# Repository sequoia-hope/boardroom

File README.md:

# Boardroom

**Boardroom is the home of a board design suite**: KiCad boards designed with
[Claude Code](https://claude.com/claude-code), from requirements to fab outputs. It holds the
design skill, the board project template, and the app that lists your projects and launches the
other suite apps. It also defines the format every board repo in the suite follows.

> **Migration under way (2026-11).** Boardroom is becoming one program with many crates:
> Projects, Compose and Route as modes of one app, with the router rewritten here
> ([`docs/one-system-spec.md`](docs/one-system-spec.md)). So far: one Cargo workspace (`crates/`),
> the web app at `web/`, pcbview in the tree as `view/`, and no submodules. The KiCad reader, the
> board model, the renderer and the intent, recognition and judging crates are in (`crates/kicad`,
> `board`, `scene`, `render`, `wasm`, `intent`, `recognise`, `library`, `interfaces`, `examine`),
> with Composer's `packages/` and `library/`. Not
> working until their crates arrive: Compose and Route. Sections below that describe
> separate repos and submodules describe board repos made so far, which stay on their pins.

**Try it:** [sequoia-hope.github.io/boardroom](https://sequoia-hope.github.io/boardroom/) is a
read-only copy of the app, open on the worked example, easy2350.

**For an agent pointed here:** this README is the map. It says what each project in the suite is,
where its repo and live page are, what a board repo looks like, and how to make one that works
with the viewer, the router and the other apps. Follow the links for detail. The specs under
[`docs/`](docs/) are the full design; [`CLAUDE.md`](CLAUDE.md) holds the rules for this repo, and
[`template/CLAUDE.md`](template/CLAUDE.md) holds the rules for a board repo.

## The suite

| Project | What it does | Repo | Live page | How a board repo uses it |
|---|---|---|---|---|
| **Boardroom** | Design skill, project template and phase gates. The app is the suite's main window: project list, status, the other apps in tabs | [sequoia-hope/boardroom](https://github.com/sequoia-hope/boardroom) | [app demo](https://sequoia-hope.github.io/boardroom/) | **`scripts/new-board.sh` makes a board repo** from `template/`, the skill and the pinned submodules |
| **pcbview** | Schematic, PCB and 3D viewer for KiCad boards, laid out after Altium 365's. Output is a static site that runs on GitHub Pages | [sequoia-hope/pcbview](https://github.com/sequoia-hope/pcbview) | in use: [robot-link](https://sequoia-hope.github.io/robot-link/), [round-pendant](https://sequoia-hope.github.io/round-pendant/) | **Git submodule** at `vendor/pcbview`, built by `scripts/view.sh` |
| **UltraRoute** | KiCad autorouter (`ultraroute route`, Rust, MIT), judged by KiCad's own DRC. **UltraRoute Studio** is its live, interactive view | [sequoia-hope/ultraroute](https://github.com/sequoia-hope/ultraroute) | [Studio](https://sequoia-hope.github.io/ultraroute/) (routes in the browser, WASM) | **Git submodule** at `vendor/ultraroute`, built by `scripts/route.sh` on first use |
| **Circuit Composer** | The stage between schematic and routing: verified chip packages, cited intent files, floorplanning, locked critical blocks, rules and cost grids for the router | [sequoia-hope/circuit-composer](https://github.com/sequoia-hope/circuit-composer) | [app](https://sequoia-hope.github.io/circuit-composer/) | **A tool you install** (`ccomp` CLI and its app). It reads `design/nets.csv` and writes under `compose/` |
| **Waffle Iron** | Parametric mechanical CAD in the browser: enclosures and mechanics around the board | [sequoia-hope/waffle-iron](https://github.com/sequoia-hope/waffle-iron) | [app](https://sequoia-hope.github.io/waffle-iron/) | **A linked project**, usually its own repo. Shares the board outline through `interface/` |
| **board-interface** | Rust crate that reads, writes, hashes and compares the shared board outline files (`board-shape.dxf` + `.json`) | [sequoia-hope/board-interface](https://github.com/sequoia-hope/board-interface) | | **Used by the apps, not the board repo.** Composer and Waffle Iron pin a tag of it |
| **board-draw** | Rust/WASM and WebGL2 board renderer shared by Studio and Composer, so both draw a board the same way | [sequoia-hope/board-draw](https://github.com/sequoia-hope/board-draw) | | **Used by the apps, not the board repo** |

**Submodule or not:** a board repo pins only the tools its own files depend on, **pcbview and
ultraroute**, as git submodules. A route depends on the exact router version, so pinning it per
project is deliberate. Circuit Composer and Waffle Iron are apps that open the board repo. They
are not vendored into it. board-interface and board-draw are libraries inside those apps.

### How the pieces connect

The apps talk through the board repo's files, never through each other's internals.
**KiCad files are the shared truth** for the schematic and the board. Each app owns its own
directory and doesn't write in another's.

```
requirements ─▶ Boardroom skill: phases 0–3 ─▶ hw/<board>/<variant>/*.kicad_sch, design/nets.csv
                                                   │
                     Circuit Composer (ccomp) ◀────┘  intent, packages, floorplan, locked blocks
                                │                     ─▶ compose/<board>/, placed .kicad_pcb
                                ▼
                     UltraRoute (route.sh / Studio)   routes the rest ─▶ routed .kicad_pcb
                                │
                                ▼
          Boardroom skill: phases 8–10, pcbview build ─▶ viewer/, fab outputs, index.html

          Waffle Iron ◀──── interface/<board>/board-shape.{dxf,json} ────▶ Circuit Composer
                       (board outline: one side drives, the other is locked until it takes over)
```

## A board repo

Every board in the suite lives in a repo with this layout. `scripts/new-board.sh` assembles it
from `template/` plus the copied skill (`.claude/skills/pcb-design/`), shared scripts
(`scripts/{doctor,view,route}.sh`), and pinned submodules (`vendor/{pcbview,ultraroute}`):

```
CLAUDE.md                    tells Claude to use the skill and follow its gates
.claude/skills/pcb-design/   the design skill, vendored: phases, gate checklists, review prompts, LESSONS.md
design/
  status.json                headline state: phase, what Claude is doing, what it needs from you, gates, checks
  intent.md                  requirements, each numbered (phase 0)
  nets.csv                   net classes (phase 3; Circuit Composer imports it)
  decisions.md               why each choice was made
  gates/                     one file per passed gate, with real tool output as evidence
  links.toml                 links to Waffle Iron projects (suite spec; planned)
hw/<board>/<variant>/        KiCad projects, one per board variant, e.g. hw/main/a/
compose/<board>/             Circuit Composer's files (written by Composer only)
route/<board>/               UltraRoute Studio's jobs and route recipe
interface/<board>/           board-shape.dxf + board-shape.json, the shared outline (written only by board-interface)
pcbview.toml                 which boards the viewer builds, and which one index.html embeds
index.html                   the project page: status from design/status.json, plus the embedded viewer
vendor/pcbview/              submodule: the viewer
vendor/ultraroute/           submodule: the autorouter
scripts/doctor.sh            checks KiCad, Python and the rest are installed
scripts/view.sh              builds the viewer
scripts/route.sh             builds and runs the router
serve.sh                     serves the project page: ./serve.sh --port N
```

Rules an agent must keep:

- **Never edit `vendor/` or `viewer/` by hand.** Bump a submodule to change a tool, and rebuild
  the viewer to change `viewer/`.
- **Update `design/status.json` and rebuild the viewer at every gate.** The Boardroom app and
  `index.html` both read `status.json`. Its version 1 schema is in
  [`docs/shell-spec.md`](docs/shell-spec.md#statusjson-version-1). Each app writes only under its
  own `apps.<name>` key.
- **Ports come from the caller.** `serve.sh` takes `--port`, then `$PORT`, and fails if it has
  neither. Don't hardcode one.
- **Corrections become lessons.** When the person corrects Claude, the rule goes into
  `.claude/skills/pcb-design/LESSONS.md`.

Repos made this way: [easy2350](examples/easy2350/) (in this repo, the worked example),
[simple-earring](https://github.com/sequoia-hope/simple-earring).

## Start a board

1. **Make your repo.** Clone Boardroom with its submodules, then run `scripts/new-board.sh`:
   ```sh
   git clone --recurse-submodules https://github.com/sequoia-hope/boardroom
   cd boardroom
   scripts/new-board.sh ~/pcb/my-board --name "My board"
   cd ~/pcb/my-board
   ```
   Pass `--github <you>/<my-board>` (and `--private` if private) to create the GitHub repo and
   push in the same step:
   ```sh
   scripts/new-board.sh ~/pcb/my-board --name "My board" --github <you>/<my-board>
   ```
   If `~/.config/boardroom/projects.toml` exists, `new-board.sh` adds the new folder to it.

2. **Check your tools.**
   ```sh
   scripts/doctor.sh
   ```
   You need KiCad 9+ (`kicad-cli`), Python 3.11+ and numpy. KiCad's Python module and ngspice
   are recommended. Routing needs Rust (`cargo`).

3. **Serve the project page** in a second terminal:
   ```sh
   ./serve.sh --port N
   ```
   and open `http://localhost:N/`. To check from your phone, use the machine's address on your
   network instead of `localhost`.

4. **Start Claude Code** in the repo and describe the board:
   ```sh
   claude
   > Let's design a board: a USB-C powered controller for two 12 V DC motors, about 50 × 80 mm.
   ```
   Claude starts at phase 0 and asks about everything the description leaves open. It stops for
   your sign-off at phases 0, 4 and 10, and whenever `design/status.json` has a question for you,
   the page shows it under **Needs you**.

New to the flow? Read [`examples/easy2350/`](examples/easy2350/) first. It shows what each gate
produces on a real board.

## The phases

| # | Phase | You sign off? |
|---|-------|---|
| 0 | Design intent: every requirement gets a number | **yes** |
| 1 | Architecture and parts, each audited against its datasheet | |
| 2 | Schematic, drawn to read like a person drew it | |
| 3 | Net classification | glance |
| 4 | Mechanical and layout brief: outline, connectors, layers | **yes** |
| 5 | Stackup and design rules | |
| 6 | Placement | review render |
| 7 | Routing: pours, short critical routes, the autorouter for the rest | |
| 8 | Simulation and signal integrity | |
| 9 | Silkscreen and art | review render |
| 10 | Release: fab outputs, sync and rotation checks, final review | **yes** |

Each phase ends at a **gate**: a checklist with real tool output as evidence, reviewed by a
separate fresh-context agent before the work moves on. The details are in
`.claude/skills/pcb-design/SKILL.md` and its `references/`.

## The viewer: pcbview

pcbview turns a KiCad project into a static site with schematic, PCB and 3D tabs and a part
pane. It runs on a phone and needs no server code. List your boards in `pcbview.toml`, one
`[[boards]]` entry per variant:

```toml
title = "My board"
out = "viewer"
back = { href = "../index.html", label = "Project page" }
repo = "https://github.com/<you>/<your-board>"   # open-source projects only

[[boards]]
id = "main-a"
name = "Main board, variant A"
pcb = "hw/main/a/main.kicad_pcb"
sch = "hw/main/a/main.kicad_sch"
embed = "index.html"                 # the board the project page shows
```

Then build it. Claude does this at every gate:

```sh
scripts/view.sh build pcbview.toml       # all boards -> viewer/, and the one marked embed into index.html
scripts/view.sh models pcbview.toml      # which parts have no 3D model, and why
```

Every option is in [pcbview's README](https://github.com/sequoia-hope/pcbview#the-config-file).

**Publishing on GitHub Pages:** `viewer/` is gitignored by default. To publish, remove that line
from `.gitignore`, add an empty `.nojekyll` file at the root, commit the build, and turn on Pages
for the branch root in the repo's settings. `index.html` and `viewer/` are plain static files,
so nothing else is needed. [robot-link](https://github.com/sequoia-hope/robot-link) and
[round-pendant](https://github.com/sequoia-hope/round-pendant) are published this way.

## Routing: UltraRoute

Phase 7 lays pours and short critical routes by hand, then routes the rest with ultraroute.
`scripts/route.sh` builds the pinned submodule into `build/` on first use, and the skill's
`autoroute.py` runs it seed by seed and judges each result with KiCad's DRC. Missing router
features go to the [ultraroute project](https://github.com/sequoia-hope/ultraroute) as requests,
not as workaround scripts in the board repo. To watch or steer a route, open the board in
[UltraRoute Studio](https://sequoia-hope.github.io/ultraroute/).

## Composition: Circuit Composer

Circuit Composer covers the stage between schematic and routing. Install it from
[its repo](https://github.com/sequoia-hope/circuit-composer#build-and-run). Then:

```sh
ccomp import easy-pcb design/nets.csv --board <board> \
    --netlist hw/<board>/<variant>/<board>.kicad_sch -o draft.json   # phase-3 net classes -> a draft intent file
ccomp -C . floorplan --seed 2               # place the project's only board
ccomp check package <board>.kicad_pcb --package <pkg> --binding <binding.json>
```

It keeps its files under `compose/<board>/` and hands UltraRoute a placed board, with critical
blocks locked (KiCad's own `(locked yes)`) and rules and cost grids for the rest.

## Mechanical: Waffle Iron and the shared outline

A Waffle Iron project and a Boardroom project **stay linked for as long as the product is being
developed**. The board outline can be drawn in Waffle Iron or in Circuit Composer. One side drives
it at a time, the other shows it locked, and the drive changes hands only when someone takes it
over. The outline crosses in two files that only
[board-interface](https://github.com/sequoia-hope/board-interface) writes:

```
interface/<board>/board-shape.dxf     outline, cutouts, holes, keepouts, each with a stable ID
interface/<board>/board-shape.json    revision, parent, author, driver, thickness, geometry hash
```

Each side records the other's commit, either pinned or following a branch, and sees when it is
behind. Today Waffle Iron imports a `.kicad_pcb` one way. The two-way outline is specified and
partly built. [`docs/suite-spec.md`](docs/suite-spec.md) has the full design, and its "What exists
today" table says what works now.

## The Boardroom app

The app lists your board projects, shows each one's status, gates and renders, and opens
Waffle Iron in a tab on one origin. Compose and Route are becoming modes of the app itself.

```sh
./build.sh                                    # build the web app, the boardroom binary and the desktop window
./serve.sh --port N                           # serve it
target/release/boardroom-gtk                  # desktop window (GTK 4 / WebKitGTK); crates/gtk/install-desktop.sh adds a launcher
target/release/boardroom open                 # or a Chrome app window
```

The project list is `~/.config/boardroom/projects.toml`, and machine paths, such as a Waffle Iron
build, are in `~/.config/boardroom/config.toml`. Any folder with `design/status.json` opens as a
project. A passed gate records what it judged (`design/gates/phaseN.inputs.json`, written by
`gate_inputs.py record N`), and the app marks it stale with the reason when one of those inputs
changes. The Versions tab shows linked projects and what a release was built against.

The Terminal tab runs a real `claude` session in the project folder. The server owns it, so it
survives closing the page. It accepts only this machine, and only Boardroom's own page. With
`waffle_relay = "uv run --project <waffle-iron>/relay waffle-mcp-relay"` in `config.toml`, the
session gets Waffle Iron's tools. The relay's port is `proj port boardroom-waffle-relay`.

The read-only copy on [GitHub Pages](https://sequoia-hope.github.io/boardroom/) is built
by `.github/workflows/pages.yml` from snapshots of the projects in `examples.toml`.

## Specs

| Spec | Covers |
|---|---|
| [`docs/platform-spec.md`](docs/platform-spec.md) | The suite: Boardroom, Composer, UltraRoute, and the file seam between them |
| [`docs/shell-spec.md`](docs/shell-spec.md) | The Boardroom app, the project format, `status.json` v1, the vendored skill |
| [`docs/demo-spec.md`](docs/demo-spec.md) | The whole workflow running on GitHub Pages |
| [`docs/suite-spec.md`](docs/suite-spec.md) | Waffle Iron with Boardroom: linked projects, the shared outline, version tracking |
| [`docs/kicad-extension-spec.md`](docs/kicad-extension-spec.md) | Boardroom for KiCad: a standalone package for KiCad users, selection both ways, routing into the open board (draft) |
| [`docs/one-system-spec.md`](docs/one-system-spec.md) | **The migration under way:** Boardroom as one program with many crates (Projects, Compose, Route), the router rewritten here, no history import |
| [`docs/monorepo-spec.md`](docs/monorepo-spec.md) | Superseded by `one-system-spec.md`; kept for its inventory of what existed |

## pcbview and the router

pcbview lives in this repository as `view/` and is edited here; `scripts/view.sh` runs it. There
is no router in this repository until the new one is written (`docs/one-system-spec.md`, step 6);
`scripts/route.sh` uses `$ULTRAROUTE` when it is set. Board repos made so far keep their
`vendor/pcbview` and `vendor/ultraroute` submodules at their pins.

## The skill learns

When you correct Claude, it adds the correction to `.claude/skills/pcb-design/LESSONS.md` as a
rule, and reads that file at the start of every session. Commit it with the rest of the project.
If a lesson applies to every board, send it upstream to this repo.

## License

MIT, see `LICENSE`. The license covers Boardroom and its template. The boards you make from it are
yours to license as you like.

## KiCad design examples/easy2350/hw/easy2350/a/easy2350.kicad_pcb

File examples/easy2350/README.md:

# easy2350: a worked example

An RP2350A development board (USB-C, 16 MB flash, all 30 GPIO on breadboard
headers, 21 × 51 mm; Pico-sized but **not** Pico pin-compatible: a Pico
carrier would put 5 V on GPIO29), designed with Boardroom's `pcb-design` skill from
phase 0 to fab outputs. Read it gate by gate:

| Phase | Gate file | State |
|---|---|---|
| 0 Design intent | [`design/gates/phase0.md`](design/gates/phase0.md) | passed, signed off (added the addressable LEDs) |
| 1 Architecture and parts | [`design/gates/phase1.md`](design/gates/phase1.md) | passed |
| 2 Schematic | [`design/gates/phase2.md`](design/gates/phase2.md) | passed |
| 3 Net classification | [`design/gates/phase3.md`](design/gates/phase3.md) | passed |
| 4 Mechanical and layout brief | [`design/gates/phase4.md`](design/gates/phase4.md) | passed |
| 5 Stackup and rules | [`design/gates/phase5.md`](design/gates/phase5.md) | passed |
| 6 Placement | [`design/gates/phase6.md`](design/gates/phase6.md) | passed |
| 7 Routing | [`design/gates/phase7.md`](design/gates/phase7.md) | passed: DRC 0 errors, 0 unconnected |
| 8 Simulation and SI | [`design/gates/phase8.md`](design/gates/phase8.md) | passed |
| 9 Silkscreen and art | [`design/gates/phase9.md`](design/gates/phase9.md) | passed |
| 10 Release | [`design/gates/phase10.md`](design/gates/phase10.md) | fab files ready, release review says send; awaiting the user's approval |

Fab files: [`hw/easy2350/a/fab/`](hw/easy2350/a/fab/) (gerbers, JLC BOM and CPL,
STEP). Bring-up: [`design/bringup.md`](design/bringup.md). Board scripts:
[`scripts/board.py`](scripts/board.py) (placement, routing, finish, silk),
[`scripts/fab.py`](scripts/fab.py).

Everything a phase produced lives in [`design/`](design/): the intent, part
audits, decisions with their reasons, and each gate's evidence and review.
The project page is [`index.html`](index.html) (viewer rebuilt from the repo root
with `scripts/view.sh build examples/easy2350/pcbview.toml`); to browse it in
Boardroom, run `app/serve.sh --port N` from the repo root and open `easy2350`.

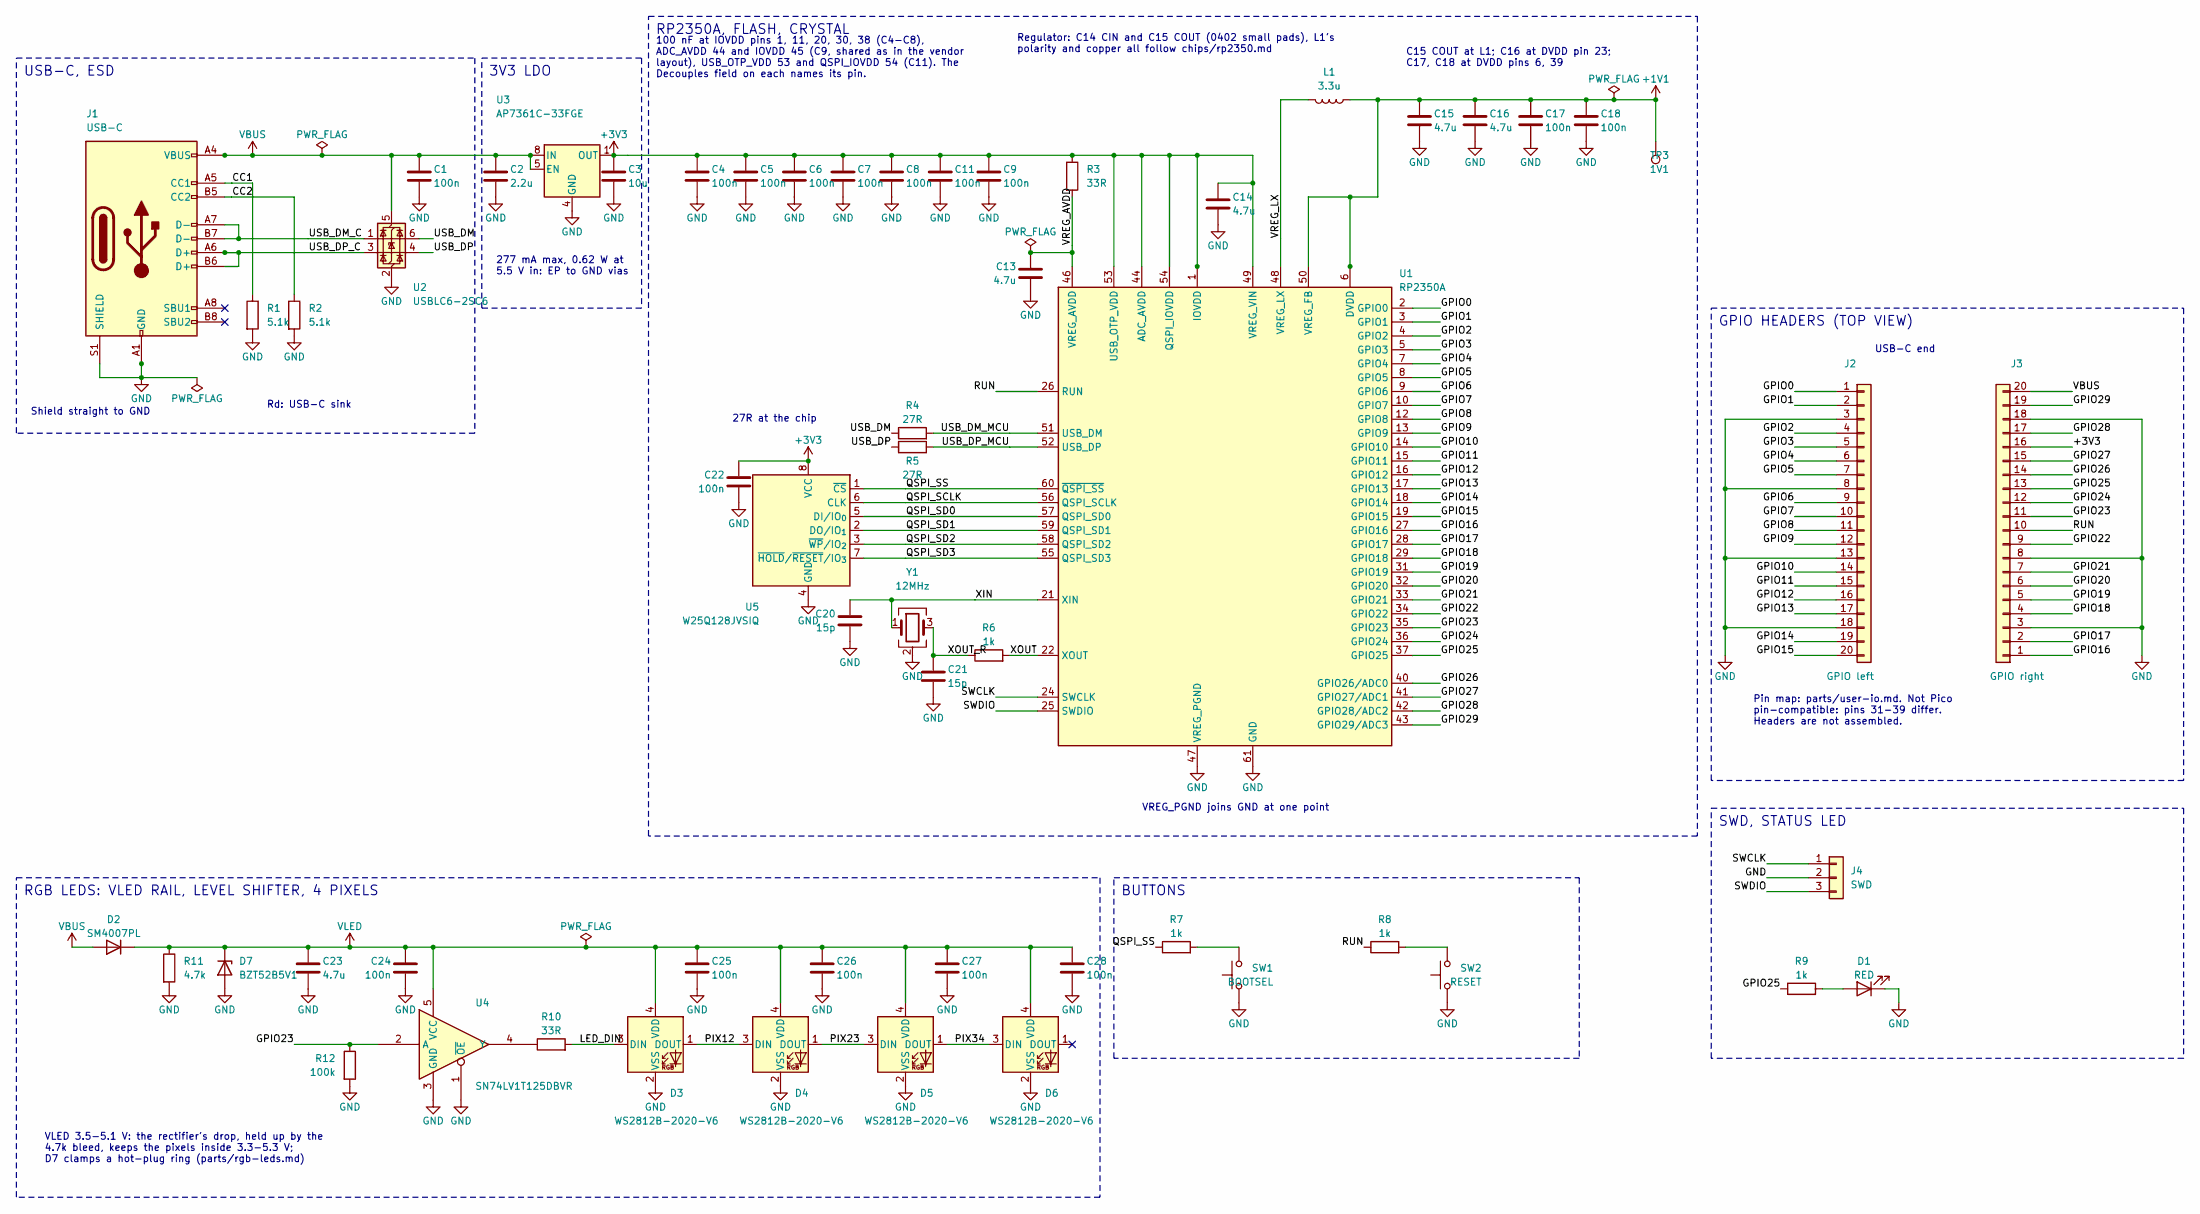
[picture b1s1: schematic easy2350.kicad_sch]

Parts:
C1, C4, C5, C6, C7, C8, C9, C11, C17, C18, C22, C24, C25, C26, C27, C28: 100n; C_0402_1005Metric; MPN CL05B104KO5NNNC; LCSC C1525
C2: 2.2u; C_0603_1608Metric; MPN CL10A225KO8NNNC; LCSC C23630
C3: 10u; C_0805_2012Metric; MPN CL21A106KAYNNNE; LCSC C15850
C13, C16: 4.7u; C_0402_1005Metric; MPN CL05A475MP5NRNC; LCSC C23733
C14, C15: 4.7u; C_0402_1005Metric_small_pads; MPN CL05A475MP5NRNC; LCSC C23733
C20, C21: 15p; C_0402_1005Metric; MPN 0402CG150J500NT; LCSC C1548
C23: 4.7u; C_0603_1608Metric; MPN CL10A475KO8NNNC; LCSC C19666
D1: RED; LED_0603_1608Metric; MPN KT-0603R; LCSC C2286
D2: SM4007PL; D_SOD-123F_MDD; MPN SM4007PL; LCSC C64898
D3, D4, D5, D6: WS2812B-2020-V6; LED_WS2812B-2020_PLCC4_2.0x2.0mm; MPN WS2812B-2020-V6; LCSC C52917434
D7: BZT52B5V1; D_SOD-123; MPN BZT52B5V1; LCSC C19077393
J1: USB-C; USB_C_Receptacle_HRO_TYPE-C-31-M-12; MPN TYPE-C-31-M-12; LCSC C165948
J2: GPIO left; PinHeader_1x20_P2.54mm_Vertical
J3: GPIO right; PinHeader_1x20_P2.54mm_Vertical
J4: SWD; PinHeader_1x03_P2.54mm_Vertical
L1: 3.3u; L_pol_2016; MPN AOTA-B201610S3R3-101-T; LCSC C42411119
R1, R2: 5.1k; R_0402_1005Metric; MPN 0402WGF5101TCE; LCSC C25905
R3, R10: 33R; R_0402_1005Metric; MPN 0402WGF330JTCE; LCSC C25105
R4, R5: 27R; R_0402_1005Metric; MPN 0402WGF270JTCE; LCSC C25100
R6, R7, R8, R9: 1k; R_0402_1005Metric; MPN 0402WGF1001TCE; LCSC C11702
R11: 4.7k; R_0402_1005Metric; MPN 0402WGF4701TCE; LCSC C25900
R12: 100k; R_0402_1005Metric; MPN 0402WGF1003TCE; LCSC C25741
SW1: BOOTSEL; SW_SPST_TS-1088-xR020; MPN TS-1088-AR02016; LCSC C720477
SW2: RESET; SW_SPST_TS-1088-xR020; MPN TS-1088-AR02016; LCSC C720477
TP3: 1V1; TestPoint_Pad_D1.0mm
U1: RP2350A; RP2350-QFN-60-1EP_7x7_P0.4mm_EP3.4x3.4mm_ThermalVias; MPN RP2350A; LCSC C42411118
U2: USBLC6-2SC6; SOT-23-6; MPN USBLC6-2SC6; LCSC C7519
U3: AP7361C-33FGE; DFN-8-1EP_3x3mm_P0.65mm_EP1.5x2.25mm_ThermalVias; MPN AP7361C-33FGE-7; LCSC C151007
U4: SN74LV1T125DBVR; SOT-23-5; MPN SN74LV1T125DBVR; LCSC C473338
U5: W25Q128JVSIQ; SOIC-8_5.3x5.3mm_P1.27mm; MPN W25Q128JVSIQ; LCSC C97521
Y1: 12MHz; Crystal_SMD_3225-4Pin_3.2x2.5mm; MPN ABM8-272-T3; LCSC C20625731

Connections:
+3V3: C3.1, C4.1, C5.1, C6.1, C7.1, C8.1, C9.1, C11.1, C14.1, C22.1, J3.16, R3.1, U1.1 (IOVDD), U1.11 (IOVDD), U1.20 (IOVDD), U1.30 (IOVDD), U1.38 (IOVDD), U1.44 (ADC_AVDD), U1.45 (IOVDD), U1.49 (VREG_VIN), U1.53 (USB_OTP_VDD), U1.54 (QSPI_IOVDD), U3.1 (OUT), U5.8 (VCC)
/CC1: J1.A5 (CC1), R1.1
/CC2: J1.B5 (CC2), R2.1
/GPIO0: J2.1, U1.2 (GPIO0)
/GPIO1: J2.2, U1.3 (GPIO1)
/GPIO2: J2.4, U1.4 (GPIO2)
/GPIO3: J2.5, U1.5 (GPIO3)
/GPIO4: J2.6, U1.7 (GPIO4)
/GPIO5: J2.7, U1.8 (GPIO5)
/GPIO6: J2.9, U1.9 (GPIO6)
/GPIO7: J2.10, U1.10 (GPIO7)
/GPIO8: J2.11, U1.12 (GPIO8)
/GPIO9: J2.12, U1.13 (GPIO9)
/GPIO10: J2.14, U1.14 (GPIO10)
/GPIO11: J2.15, U1.15 (GPIO11)
/GPIO12: J2.16, U1.16 (GPIO12)
/GPIO13: J2.17, U1.17 (GPIO13)
/GPIO14: J2.19, U1.18 (GPIO14)
/GPIO15: J2.20, U1.19 (GPIO15)
/GPIO16: J3.1, U1.27 (GPIO16)
/GPIO17: J3.2, U1.28 (GPIO17)
/GPIO18: J3.4, U1.29 (GPIO18)
/GPIO19: J3.5, U1.31 (GPIO19)
/GPIO20: J3.6, U1.32 (GPIO20)
/GPIO21: J3.7, U1.33 (GPIO21)
/GPIO22: J3.9, U1.34 (GPIO22)
/GPIO23: J3.11, R12.1, U1.35 (GPIO23), U4.2 (A)
/GPIO24: J3.12, U1.36 (GPIO24)
/GPIO25: J3.13, R9.1, U1.37 (GPIO25)
/GPIO26: J3.14, U1.40 (GPIO26/ADC0)
/GPIO27: J3.15, U1.41 (GPIO27/ADC1)
/GPIO28: J3.17, U1.42 (GPIO28/ADC2)
/GPIO29: J3.19, U1.43 (GPIO29/ADC3)
/LED_DIN: D3.3 (DIN), R10.2
/PIX12: D3.1 (DOUT), D4.3 (DIN)
/PIX23: D4.1 (DOUT), D5.3 (DIN)
/PIX34: D5.1 (DOUT), D6.3 (DIN)
/QSPI_SCLK: U1.56 (QSPI_SCLK), U5.6 (CLK)
/QSPI_SD0: U1.57 (QSPI_SD0), U5.5 (DI/IO_{0})
/QSPI_SD1: U1.59 (QSPI_SD1), U5.2 (DO/IO_{1})
/QSPI_SD2: U1.58 (QSPI_SD2), U5.3 (~WP/IO_{2})
/QSPI_SD3: U1.55 (QSPI_SD3), U5.7 (~HOLD/~RESET/IO_{3})
/QSPI_SS: R7.1, U1.60 (~QSPI_SS), U5.1 (~CS)
/RUN: J3.10, R8.1, U1.26 (RUN)
/SWCLK: J4.1, U1.24 (SWCLK)
/SWDIO: J4.3, U1.25 (SWDIO)
/USB_DM: R4.1, U2.6 (I/O1)
/USB_DM_C: J1.A7 (D-), J1.B7 (D-), U2.1 (I/O1)
/USB_DM_MCU: R4.2, U1.51 (USB_DM)
/USB_DP: R5.1, U2.4 (I/O2)
/USB_DP_C: J1.A6 (D+), J1.B6 (D+), U2.3 (I/O2)
/USB_DP_MCU: R5.2, U1.52 (USB_DP)
/VREG_LX: L1.2, U1.48 (VREG_LX)
/XIN: C20.1, U1.21 (XIN), Y1.1
/XOUT: R6.2, U1.22 (XOUT)
/XOUT_R: C21.1, R6.1, Y1.3
unnamed: D1.2 (A), R9.2
unnamed: R7.2, SW1.2
unnamed: R8.2, SW2.2
unnamed: R10.1, U4.4 (Y)

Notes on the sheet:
100 nF at IOVDD pins 1, 11, 20, 30, 38 (C4-C8), ADC_AVDD 44 and IOVDD 45 (C9, shared as in the vendor layout), USB_OTP_VDD 53 and QSPI_IOVDD 54 (C11). The Decouples field on each names its pin.
C15 COUT at L1; C16 at DVDD pin 23; C17, C18 at DVDD pins 6, 39
Regulator: C14 CIN and C15 COUT (0402 small pads), L1's polarity and copper all follow chips/rp2350.md
VREG_PGND joins GND at one point
27R at the chip
RP2350A, FLASH, CRYSTAL
Shield straight to GND
Rd: USB-C sink
USB-C, ESD
277 mA max, 0.62 W at 5.5 V in: EP to GND vias
3V3 LDO
VLED 3.5-5.1 V: the rectifier's drop, held up by the 4.7k bleed, keeps the pixels inside 3.3-5.3 V; D7 clamps a hot-plug ring (parts/rgb-leds.md)
RGB LEDS: VLED RAIL, LEVEL SHIFTER, 4 PIXELS
USB-C end
Pin map: parts/user-io.md. Not Pico pin-compatible: pins 31-39 differ. Headers are not assembled.
GPIO HEADERS (TOP VIEW)
BUTTONS
SWD, STATUS LED

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
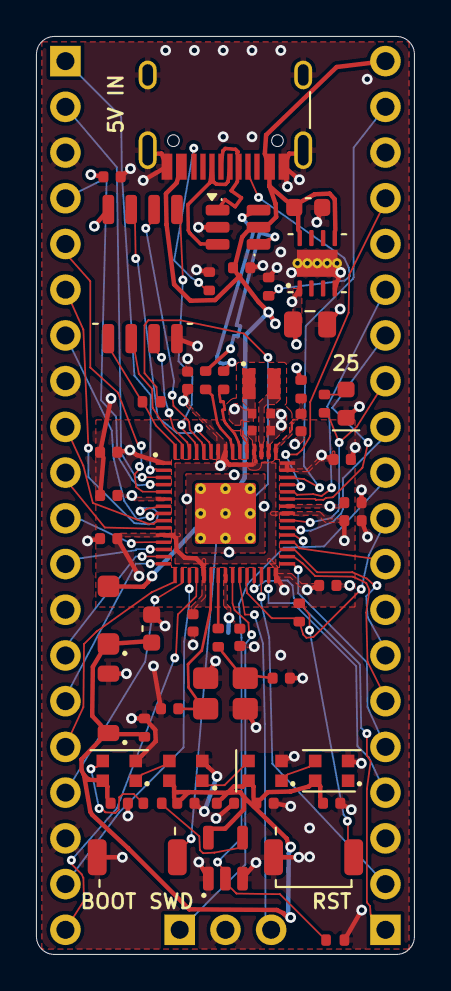
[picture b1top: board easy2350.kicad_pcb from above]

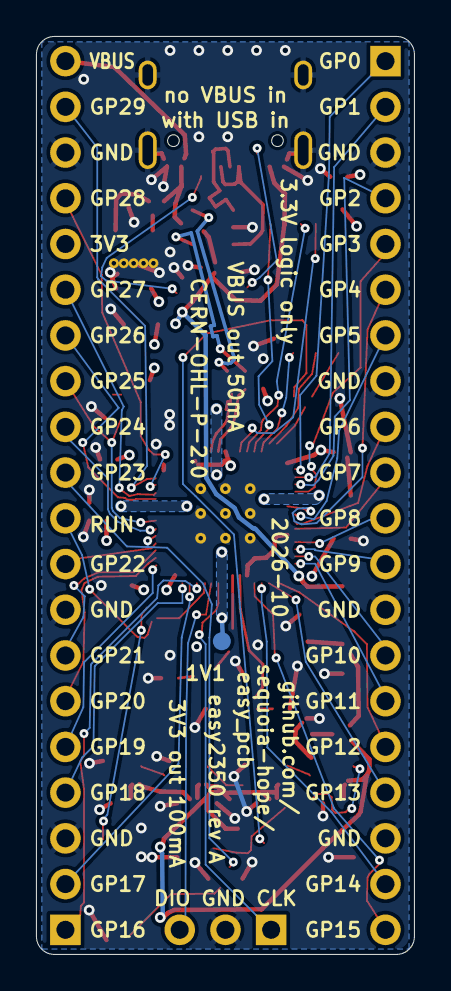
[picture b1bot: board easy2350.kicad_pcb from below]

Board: 4 copper layers, 21.0 x 51.0 mm, 58 parts (3 on the bottom side), 65 nets.

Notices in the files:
examples/easy2350/hw/easy2350/a/easy2350.kicad_pcb:
CERN-OHL-P-2.0
